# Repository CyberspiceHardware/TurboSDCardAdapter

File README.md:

# Turbo SD card adapter for Acorn Electron, BBC Micro and BBC Master

## Hardware

This board builds a Turbo SD card adapter for the Acorn 8 bit machines.
For simplicity it uses an [Adafruit Micro SD Breakout](https://www.adafruit.com/product/254).

To support Turbo mode it needs a single 74HCT125 quad tri state buffer
chip in a SOIC package. However you can leave that off and build it in
non turbo mode by linking pads 2 and 3 together, and pads 8 and 9 together
as this permanently connects CB2 to Data Out on the SD card, and PB0 to
Data In on the SD card. 

## Software

This adapter is compatible with [MMFS](https://github.com/hoglet67/MMFS) by Hoglet.

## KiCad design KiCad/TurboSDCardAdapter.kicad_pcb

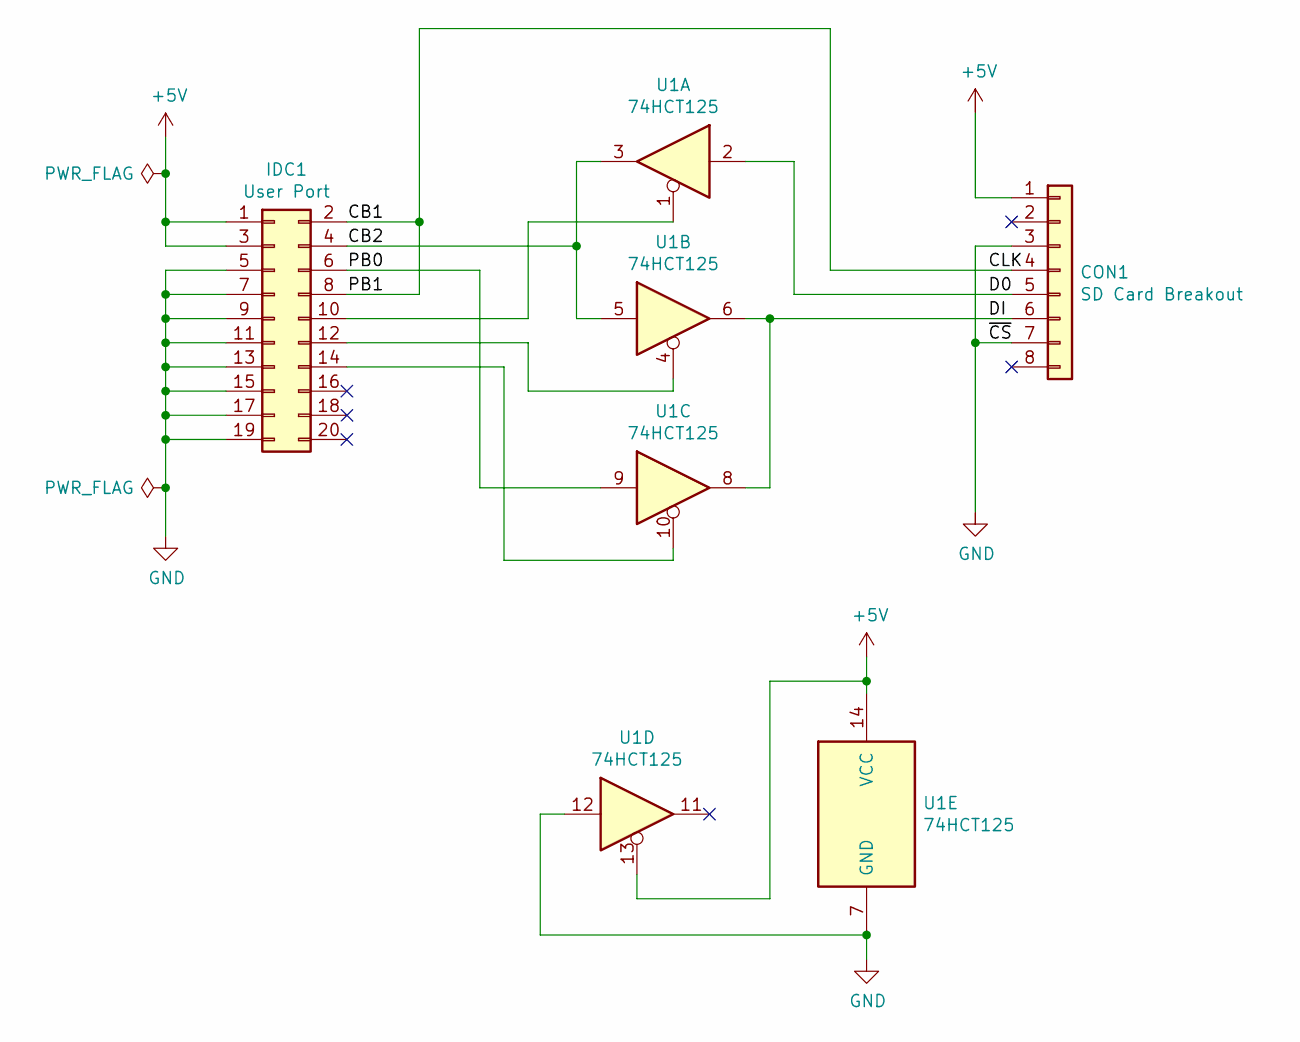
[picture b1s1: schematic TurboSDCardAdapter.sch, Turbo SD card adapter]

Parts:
CON1: SD Card Breakout; PinSocket_1x08_P2.54mm_Vertical
IDC1: User Port; IDC-Header_2x10_P2.54mm_Vertical
U1: 74HCT125; SOIC-14_3.9x8.7mm_P1.27mm

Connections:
+5V: CON1.1, IDC1.1, IDC1.3, U1.13, U1.14 (VCC)
/CB1: CON1.4, IDC1.2, IDC1.8
/CB2: IDC1.4, U1.3, U1.5
/D0: CON1.5, U1.2
/DI: CON1.6, U1.6, U1.8
/PB0: IDC1.6, U1.9
GND: CON1.3, CON1.7, IDC1.5, IDC1.7, IDC1.9, IDC1.11, IDC1.13, IDC1.15, IDC1.17, IDC1.19, U1.7 (GND), U1.12
unnamed: IDC1.10, U1.1
unnamed: IDC1.12, U1.4
unnamed: IDC1.14, U1.10

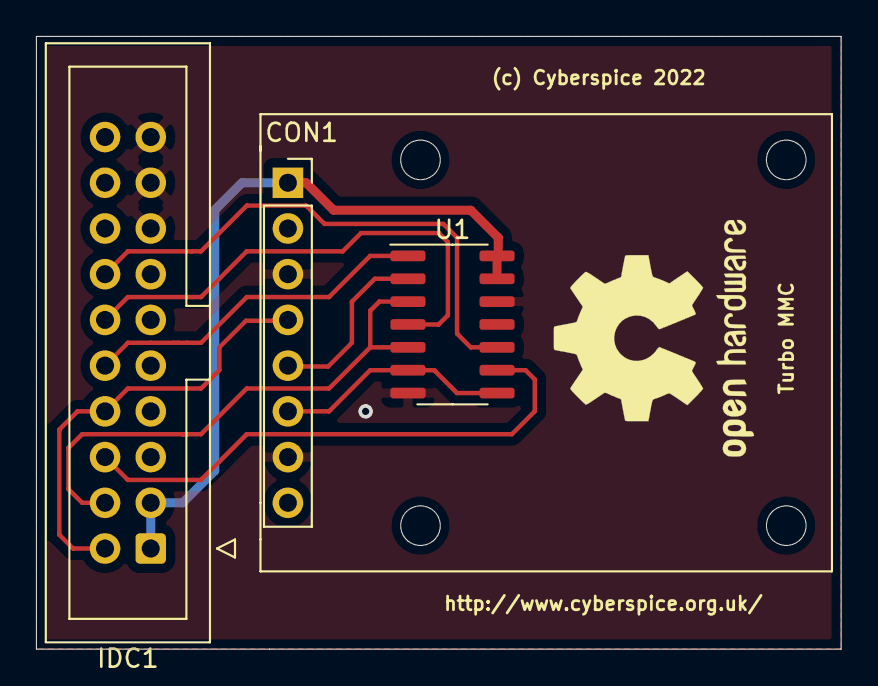
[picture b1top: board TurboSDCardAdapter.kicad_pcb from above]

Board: 2 copper layers, 44.7 x 34.0 mm, 3 parts (0 on the bottom side), 10 nets.

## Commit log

2022-03-16 Added LICENSE file.
